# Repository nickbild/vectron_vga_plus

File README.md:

# Vectron VGA Plus

Vectron VGA Plus generates a 640x480@60Hz VGA signal and has an interface that works with retro computers or microcontrollers.

Screenshot of Vectron VGA Plus running a demo:

## How It Works

I previously built a massive 7400-logic based VGA generator called [Vectron VGA](https://github.com/nickbild/vectron_vga).  While it was a nice project to build, it is huge, and not very practical to keep around for use in lots of other projects.  I built Vectron VGA Plus as a much smaller, simpler alternative.

The key change that simplified the design was to use more RAM and less logic.  So, for example, instead of having counters and flip flops, etc. to time each horizontal sync, that logic is embedded in the data in memory.  This new design was also used to create a PCB, and the KiCad files are [here](https://github.com/nickbild/vectron_vga_plus/tree/main/vectron_vga_plus_design).

The general overview of the design goes like this: a 25.175 MHz pixel clock (divided in half by a flip flop) is used to trigger a chain of 4 bit counter chips.  These counters form an address in memory, and bits from the data stored at that memory location represent red, green, blue, horizontal sync, and vertical sync.  When the end of a frame is reached, magnitude comparators reset the counters, and it all starts over for the next frame.

Of course you also need to get data *in* to the RAM, so there are some buffer chips and mode selection signals to allow an external device (e.g. retro computer or microcontroller) to take over bus control and write RAM as needed.

As I mentioned, the 25.175 MHz clock has been divided by 2, which yields a viewable resolution of 320 horizontal pixels.  To keep logic simple, the vertical resolution is kept at 480 lines, technically giving an odd resolution of 320x480, but it is expected that in actual use, the external device is going to double up horizontal lines, giving a standard resolution of 320x240.  3-bit color was implemented, yielding a palette of 8 colors.

Since even non-visible screen regions need to be represented in the RAM (for blanking periods and V-sync/H-sync timings), RAM usage is higher -- 320x480 requires 210KB of video RAM (I used a 512KB chip that I had on hand, but a 256KB chip would be sufficient).  That's a bit extravagant for the 80s-esque 6502-based retro computers that I build, but it's also, I think, within bounds for a pure retro device (as opposed to using a microcontroller or FPGA).  In addition to the reduction in chip count, this design also pays off in flexibility; timings can be tweaked by adjusting the contents of memory, even after the PCB has been finalized.

## Media

An Arduino Mega 2560 sending images to Vectron VGA Plus:

Oops!  I picked the wrong footprint for my oscillator!  Fortunately, I could still solder the pins to the pads.

Schematic:

Breadboard prototype of circuit:

## Bill of Materials

- 1 x 25.175 MHz oscillator
- 1 x 74LS74AN
- 5 x 74LS161
- 2 x SN74LS682N
- 1 x SN74HC32N
- 1 x 74LS04N
- 2 x SN74LS245N
- 4 x SN74LS244N
- 1 x AS6C4008-55PCN
- 1 x 74LS273
- 3 x 200 ohm resistors
- 3 x 100 ohm resistors
- 2 x 200 uF electrolytic capacitors
- 1 x VGA connector
- 36 x female header pins

## About the Author

[Nick A. Bild, MS](https://nickbild79.firebaseapp.com/#!/)

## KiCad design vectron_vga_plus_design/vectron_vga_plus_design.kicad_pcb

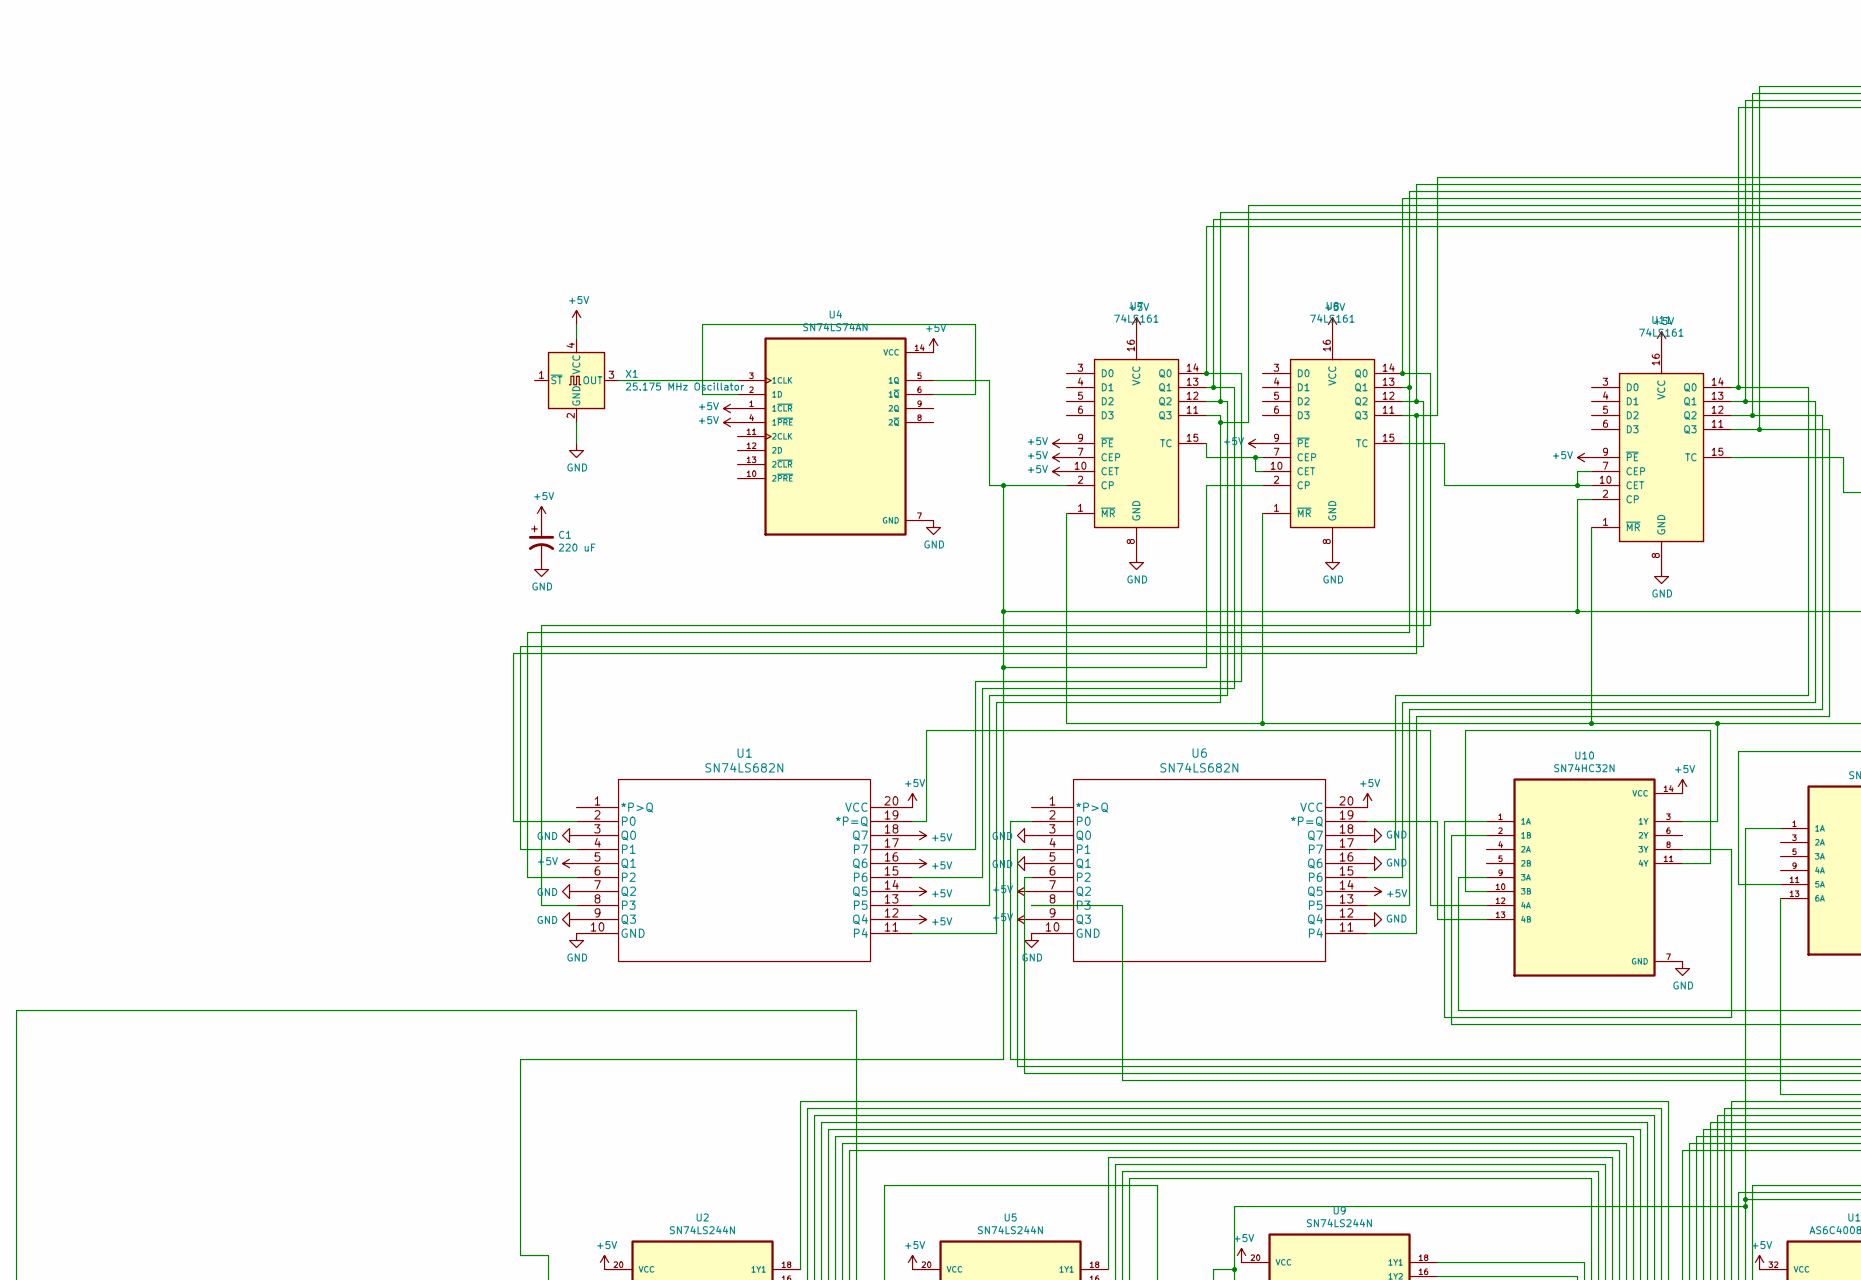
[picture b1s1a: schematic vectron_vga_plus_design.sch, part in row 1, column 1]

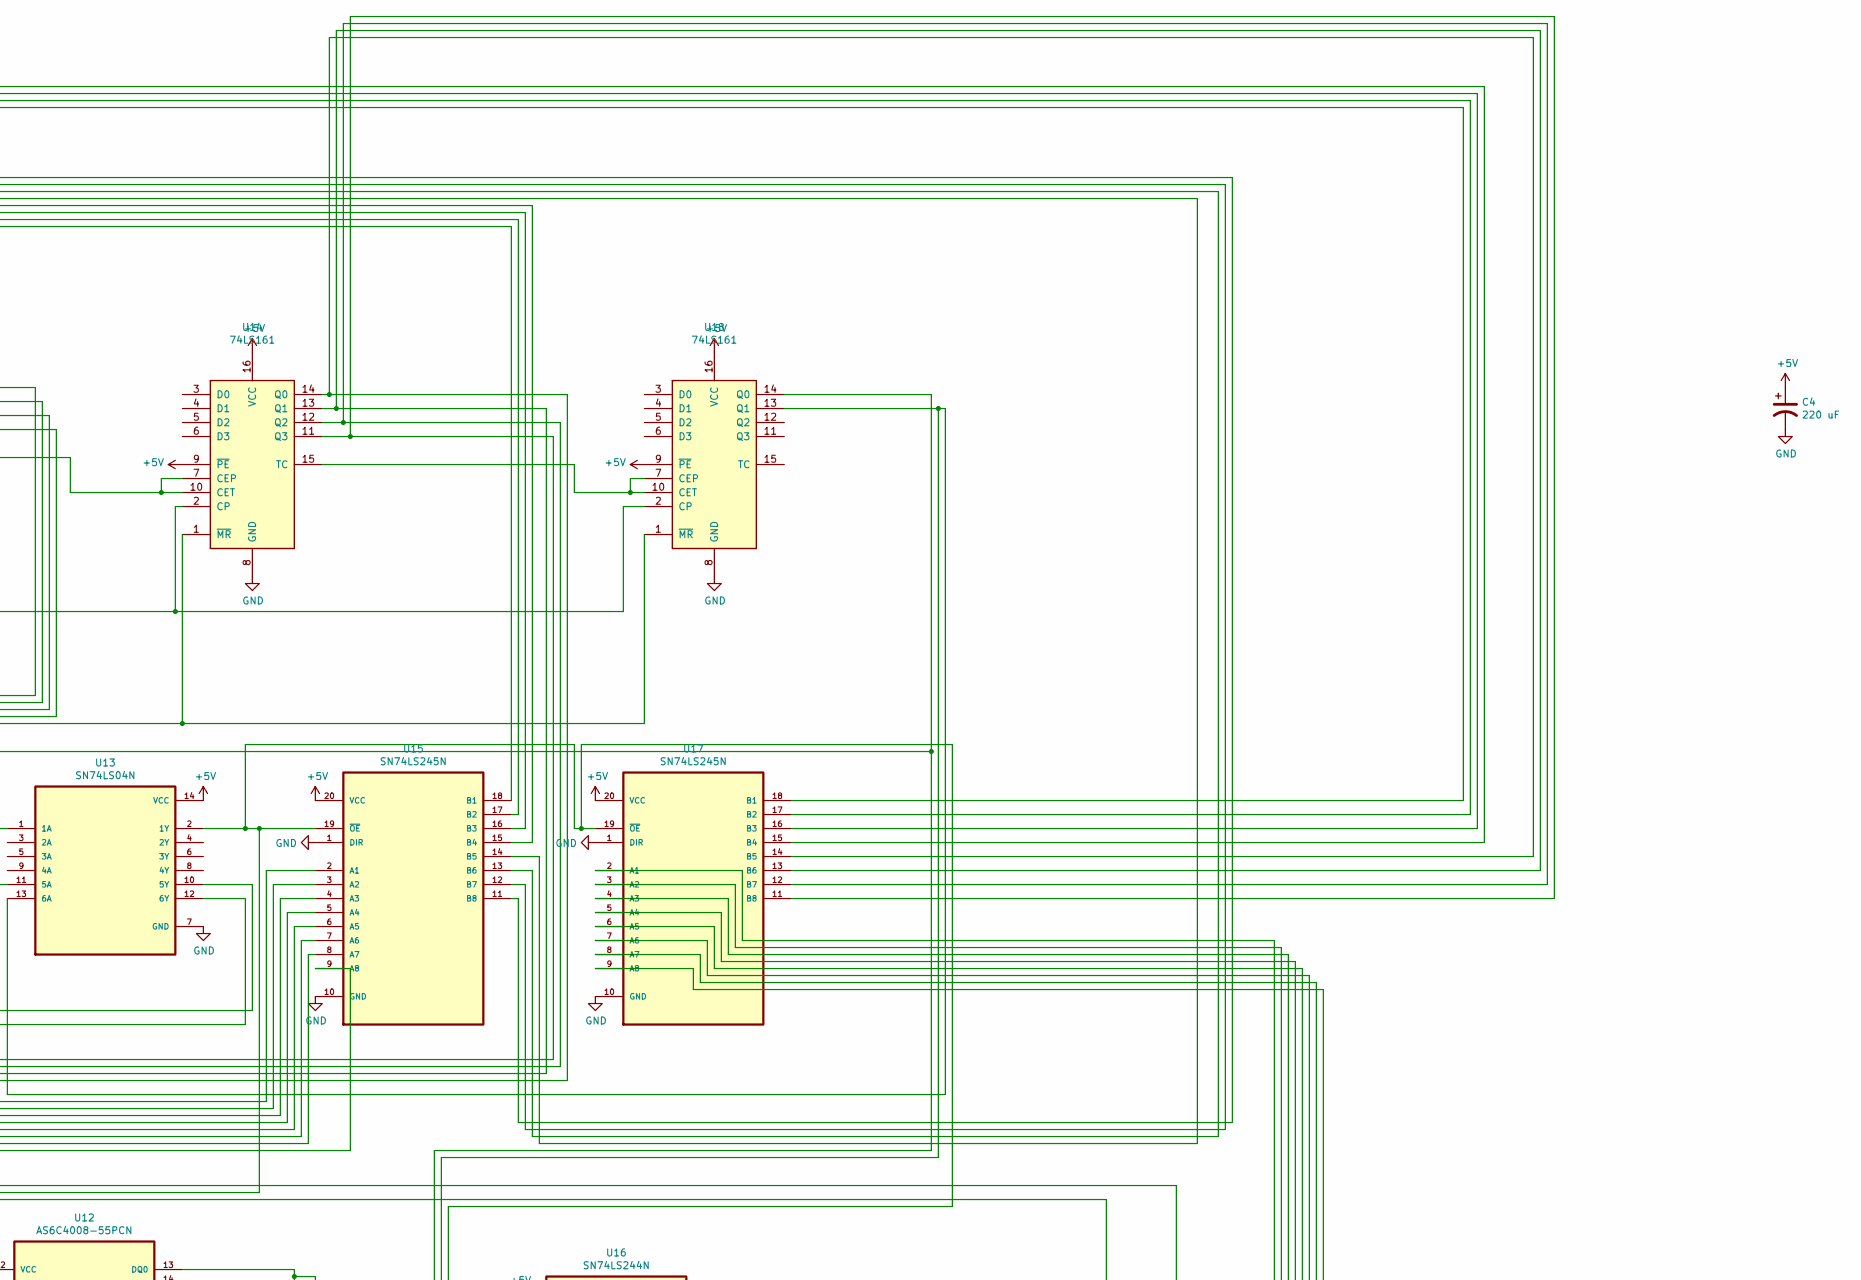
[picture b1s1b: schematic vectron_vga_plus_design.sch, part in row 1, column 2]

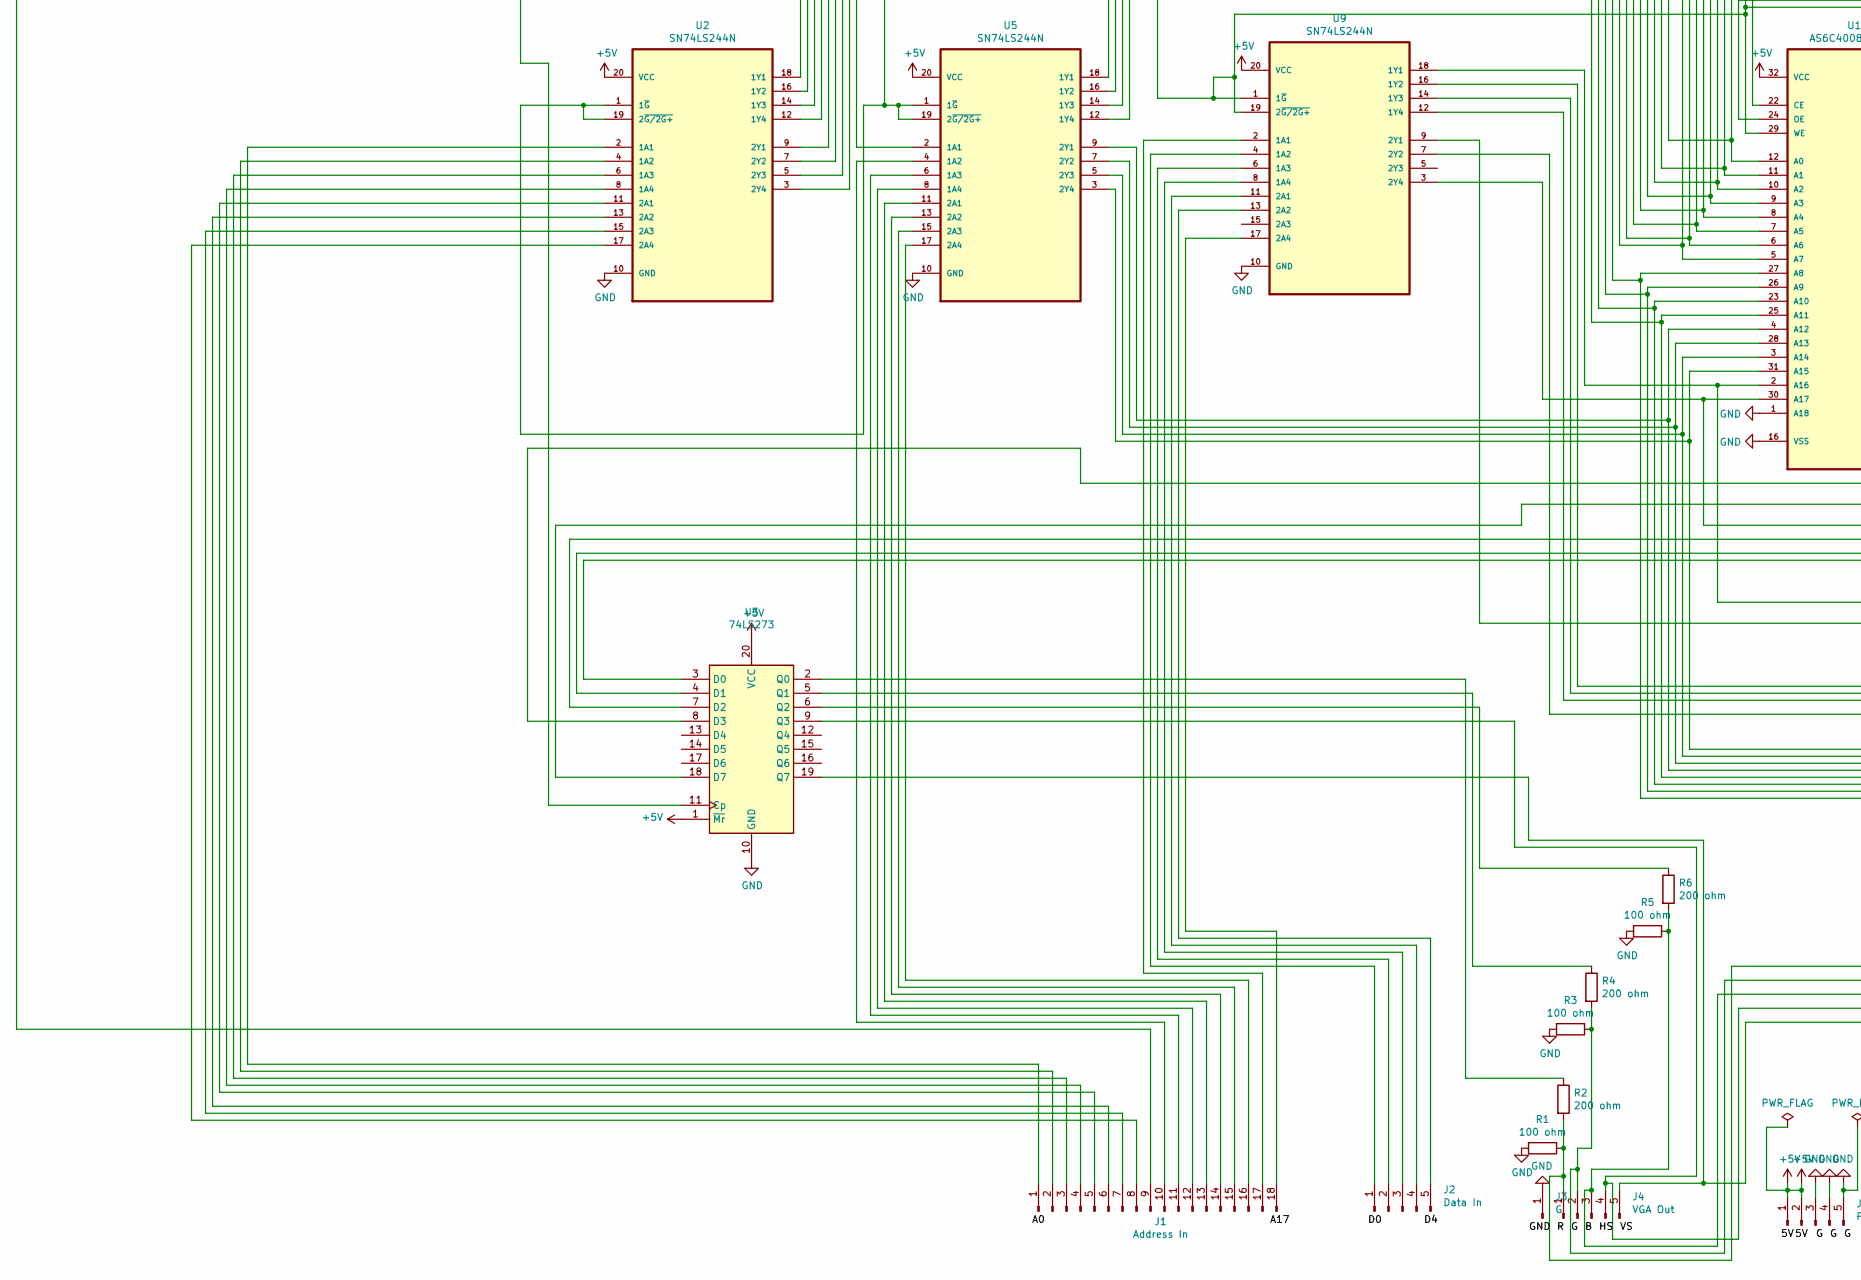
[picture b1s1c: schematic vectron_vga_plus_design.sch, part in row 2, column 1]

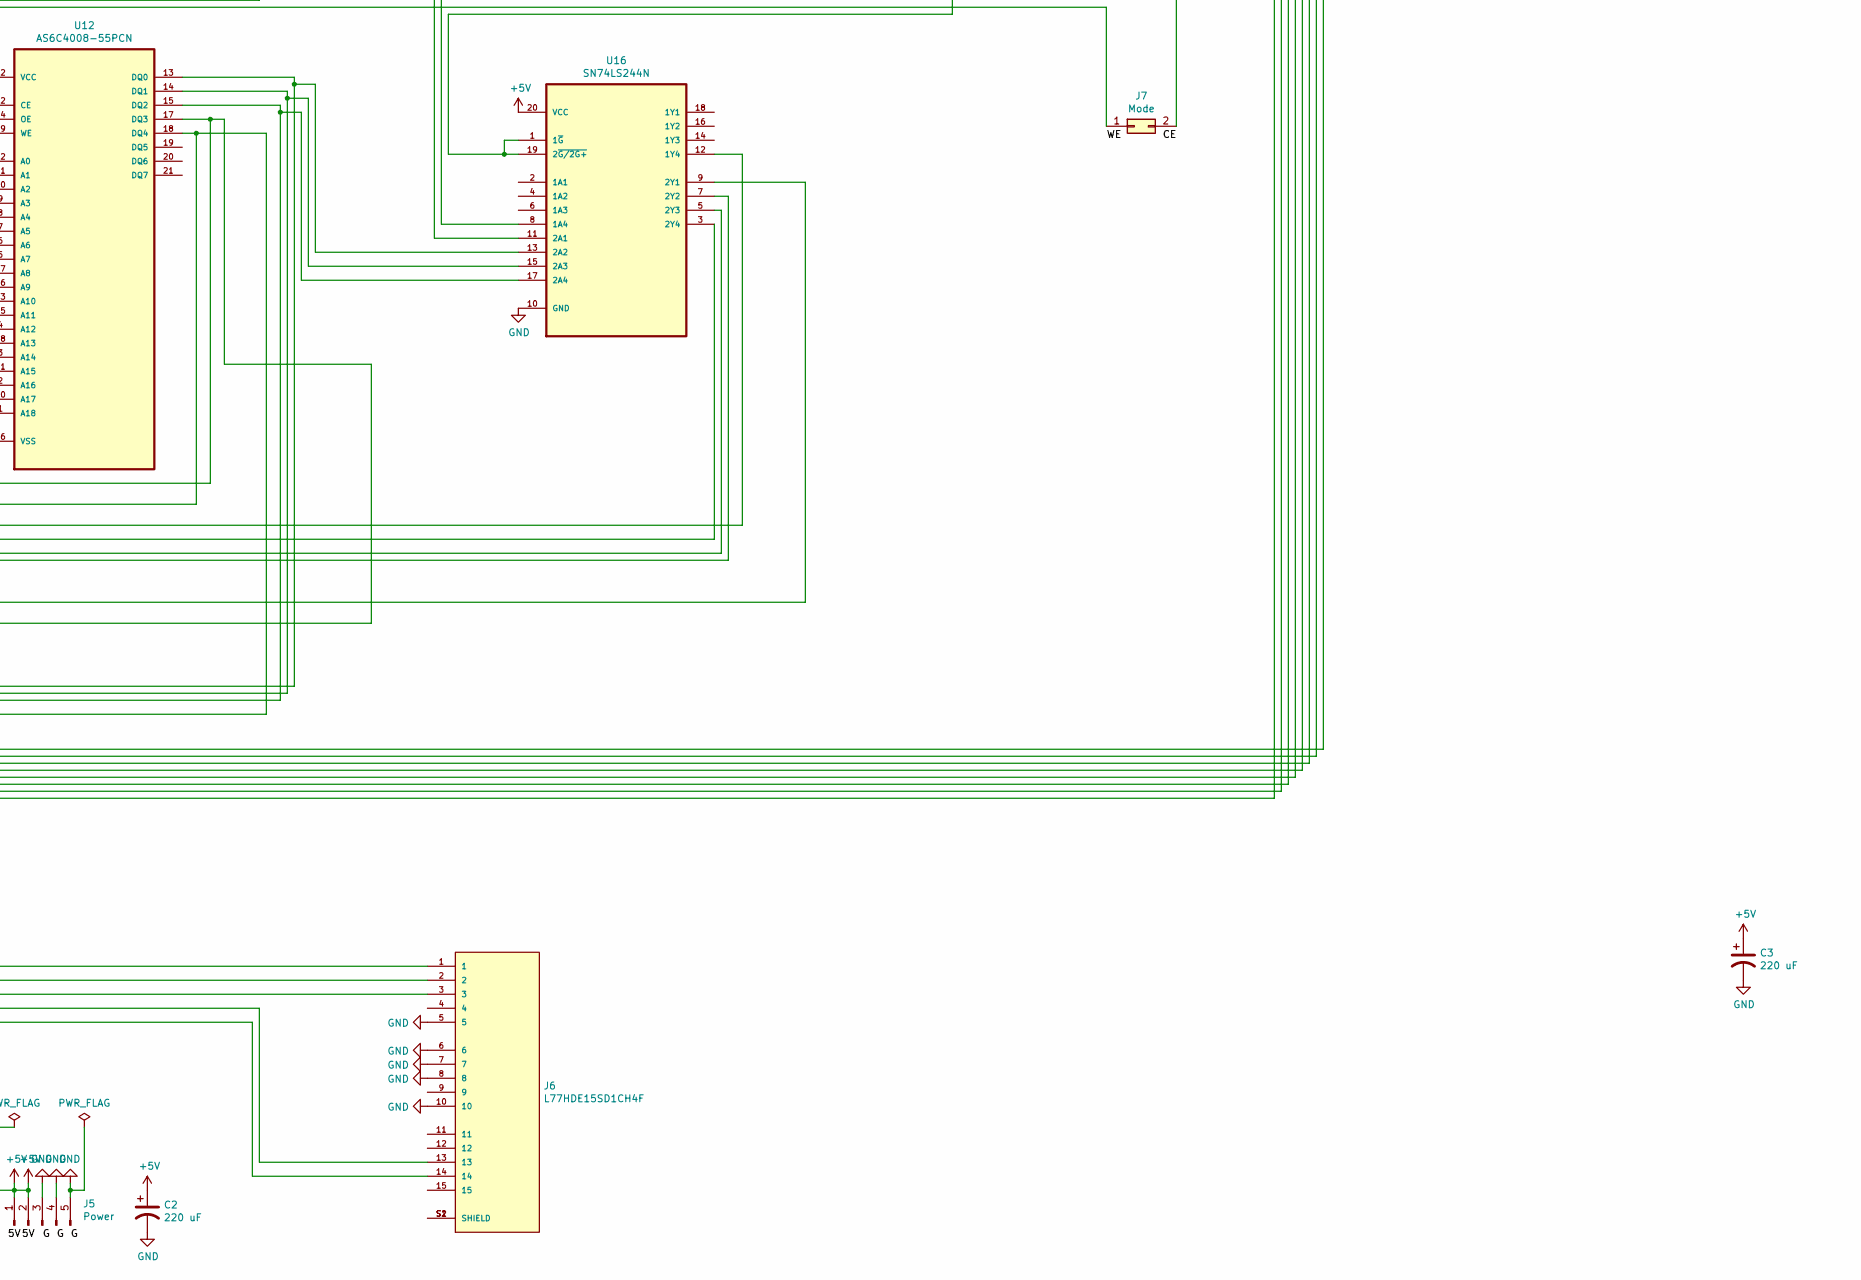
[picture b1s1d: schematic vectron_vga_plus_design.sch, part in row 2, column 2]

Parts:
C1, C2, C3, C4: 220 uF; CP_Radial_D10.0mm_P7.50mm
J1: Address In; PinHeader_1x18_P2.54mm_Horizontal
J2: Data In; PinHeader_1x05_P2.54mm_Horizontal
J3: G; PinHeader_1x01_P2.54mm_Horizontal
J4: VGA Out; PinHeader_1x05_P2.54mm_Horizontal
J5: Power; PinHeader_1x05_P2.54mm_Horizontal
J6: L77HDE15SD1CH4F; AMPHENOL_L77HDE15SD1CH4F; PARTREV N/A
J7: Mode; PinHeader_1x02_P2.54mm_Horizontal
R1, R3, R5: 100 ohm; R_Axial_DIN0207_L6.3mm_D2.5mm_P7.62mm_Horizontal
R2, R4, R6: 200 ohm; R_Axial_DIN0207_L6.3mm_D2.5mm_P7.62mm_Horizontal
U1, U6: SN74LS682N
U2, U5, U9, U16: SN74LS244N; DIP254P762X508-20; MPN SN74LS244N
U3: 74LS273; DIP254P762X508-20
U4: SN74LS74AN; DIP794W45P254L1969H508Q14
U7, U8, U11, U14, U18: 74LS161; SN74LS161AN
U10: SN74HC32N; DIP794W45P254L1969H508Q14
U12: AS6C4008-55PCN; DIP254P1524X393-32; MPN AS6C4008-55PCN
U13: SN74LS04N; DIP794W45P254L1969H508Q14
U15, U17: SN74LS245N; DIP254P762X508-20; MPN SN74LS245N
X1: 25.175 MHz Oscillator; Oscillator_SMD_SeikoEpson_SG8002CA-4Pin_7.0x5.0mm

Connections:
+5V: C1.1, C2.1, C3.1, C4.1, J5.1, J5.2, U1.5 (Q1), U1.12 (Q4), U1.14 (Q5), U1.16 (Q6), U1.18 (Q7), U1.20 (VCC), U2.20 (VCC), U3.1 (~Mr), U3.20 (VCC), U4.1 (1~CLR), U4.4 (1~PRE), U4.14 (VCC), U5.20 (VCC), U6.7 (Q2), U6.9 (Q3), U6.14 (Q5), U6.20 (VCC), U7.7 (CEP), U7.9 (~PE), U7.10 (CET), U7.16 (VCC), U8.9 (~PE), U8.16 (VCC), U9.20 (VCC), U10.14 (VCC), U11.9 (~PE), U11.16 (VCC), U12.32 (VCC), U13.14 (VCC), U14.9 (~PE), U14.16 (VCC), U15.20 (VCC), U16.20 (VCC), U17.20 (VCC), U18.9 (~PE), U18.16 (VCC), X1.4 (VCC)
/B: J4.3, J6.3, R5.1, R6.2
/G: J4.2, J6.2, R3.1, R4.2
GND: C1.2, C2.2, C3.2, C4.2, J3.1, J5.3, J5.4, J5.5, J6.5, J6.6, J6.7, J6.8, J6.10, R1.2, R3.2, R5.2, U1.3 (Q0), U1.7 (Q2), U1.9 (Q3), U1.10 (GND), U2.10 (GND), U3.10 (GND), U4.7 (GND), U5.10 (GND), U6.3 (Q0), U6.5 (Q1), U6.10 (GND), U6.12 (Q4), U6.16 (Q6), U6.18 (Q7), U7.8 (GND), U8.8 (GND), U9.10 (GND), U10.7 (GND), U11.8 (GND), U12.1 (A18), U12.16 (VSS), U13.7 (GND), U14.8 (GND), U15.1 (DIR), U15.10 (GND), U16.10 (GND), U17.1 (DIR), U17.10 (GND), U18.8 (GND), X1.2 (GND)
unnamed: J1.1, U2.2 (1A1)
unnamed: J1.2, U2.4 (1A2)
unnamed: J1.3, U2.6 (1A3)
unnamed: J1.4, U2.8 (1A4)
unnamed: J1.5, U2.11 (2A1)
unnamed: J1.6, U2.13 (2A2)
unnamed: J1.7, U2.15 (2A3)
unnamed: J1.8, U2.17 (2A4)
unnamed: J1.9, U5.2 (1A1)
unnamed: J1.10, U5.4 (1A2)
unnamed: J1.11, U5.6 (1A3)
unnamed: J1.12, U5.8 (1A4)
unnamed: J1.13, U5.11 (2A1)
unnamed: J1.14, U5.13 (2A2)
unnamed: J1.15, U5.15 (2A3)
unnamed: J1.16, U5.17 (2A4)
unnamed: J1.17, U9.2 (1A1)
unnamed: J1.18, U9.17 (2A4)
unnamed: J2.1, U9.4 (1A2)
unnamed: J2.2, U9.6 (1A3)
unnamed: J2.3, U9.8 (1A4)
unnamed: J2.4, U9.11 (2A1)
unnamed: J2.5, U9.13 (2A2)
unnamed: J4.1, J6.1, R1.1, R2.2
unnamed: J4.4, J6.13, U3.9 (Q3)
unnamed: J4.5, J6.14, U3.19 (Q7)
unnamed: J6.S1 (SHIELD), J6.S2 (SHIELD)
unnamed: J7.1, U2.1 (1~G), U2.19 (2~G/2G+), U5.1 (1~G), U5.19 (2~G/2G+), U9.1 (1~G), U9.19 (2~G/2G+), U12.29 (WE), U13.1 (1A)
unnamed: J7.2, U12.22 (CE)
unnamed: R2.1, U3.2 (Q0)
unnamed: R4.1, U3.5 (Q1)
unnamed: R6.1, U3.6 (Q2)
unnamed: U1.2 (P0), U8.11 (Q3), U15.11 (B8)
unnamed: U1.4 (P1), U8.12 (Q2), U15.12 (B7)
unnamed: U1.6 (P2), U8.13 (Q1), U15.13 (B6)
unnamed: U1.8 (P3), U8.14 (Q0), U15.14 (B5)
unnamed: U1.11 (P4), U7.11 (Q3), U15.15 (B4)
unnamed: U1.13 (P5), U7.12 (Q2), U15.16 (B3)
unnamed: U1.15 (P6), U7.13 (Q1), U15.17 (B2)
unnamed: U1.17 (P7), U7.14 (Q0), U15.18 (B1)
unnamed: U1.19 (*P=Q), U10.12 (4A)
unnamed: U4.2 (1D), U4.6 (1~Q)
unnamed: U4.3 (1CLK), X1.3 (OUT)
unnamed: U7.15 (TC), U8.7 (CEP), U8.10 (CET)
unnamed: U10.1 (1A), U10.8 (3Y)
unnamed: U10.2 (1B), U13.12 (6Y)
unnamed: U7.1 (~MR), U8.1 (~MR), U10.3 (1Y), U11.1 (~MR), U14.1 (~MR), U18.1 (~MR)
unnamed: U10.9 (3A), U13.10 (5Y)
unnamed: U10.10 (3B), U10.11 (4Y)
unnamed: U6.19 (*P=Q), U10.13 (4B)
unnamed: U3.11 (Cp), U4.5 (1Q), U7.2 (CP), U8.2 (CP), U11.2 (CP), U14.2 (CP), U18.2 (CP)
unnamed: U8.15 (TC), U11.7 (CEP), U11.10 (CET)
unnamed: U6.11 (P4), U11.11 (Q3), U17.15 (B4)
unnamed: U6.13 (P5), U11.12 (Q2), U17.16 (B3)
unnamed: U6.15 (P6), U11.13 (Q1), U17.17 (B2)
unnamed: U6.17 (P7), U11.14 (Q0), U17.18 (B1)
unnamed: U11.15 (TC), U14.7 (CEP), U14.10 (CET)
unnamed: U9.18 (1Y1), U12.2 (A16), U16.9 (2Y1)
unnamed: U5.5 (2Y3), U12.3 (A14), U17.8 (A7)
unnamed: U5.9 (2Y1), U12.4 (A12), U17.6 (A5)
unnamed: U2.3 (2Y4), U12.5 (A7), U15.9 (A8)
unnamed: U2.5 (2Y3), U12.6 (A6), U15.8 (A7)
unnamed: U2.7 (2Y2), U12.7 (A5), U15.7 (A6)
unnamed: U2.9 (2Y1), U12.8 (A4), U15.6 (A5)
unnamed: U2.12 (1Y4), U12.9 (A3), U15.5 (A4)
unnamed: U2.14 (1Y3), U12.10 (A2), U15.4 (A3)
unnamed: U2.16 (1Y2), U12.11 (A1), U15.3 (A2)
unnamed: U2.18 (1Y1), U12.12 (A0), U15.2 (A1)
unnamed: U9.16 (1Y2), U12.13 (DQ0), U16.13 (2A2)
unnamed: U9.14 (1Y3), U12.14 (DQ1), U16.15 (2A3)
unnamed: U9.12 (1Y4), U12.15 (DQ2), U16.17 (2A4)
unnamed: U3.8 (D3), U9.9 (2Y1), U12.17 (DQ3)
unnamed: U3.18 (D7), U9.7 (2Y2), U12.18 (DQ4)
unnamed: U5.14 (1Y3), U12.23 (A10), U17.4 (A3)
unnamed: U12.24 (OE), U13.2 (1Y), U15.19 (~OE), U16.1 (1~G), U16.19 (2~G/2G+), U17.19 (~OE)
unnamed: U5.12 (1Y4), U12.25 (A11), U17.5 (A4)
unnamed: U5.16 (1Y2), U12.26 (A9), U17.3 (A2)
unnamed: U5.18 (1Y1), U12.27 (A8), U17.2 (A1)
unnamed: U5.7 (2Y2), U12.28 (A13), U17.7 (A6)
unnamed: U9.3 (2Y4), U12.30 (A17), U16.12 (1Y4)
unnamed: U5.3 (2Y4), U12.31 (A15), U17.9 (A8)
unnamed: U13.11 (5A), U16.11 (2A1), U18.14 (Q0)
unnamed: U13.13 (6A), U16.8 (1A4), U18.13 (Q1)
unnamed: U6.2 (P0), U14.11 (Q3), U17.11 (B8)
unnamed: U6.4 (P1), U14.12 (Q2), U17.12 (B7)
unnamed: U6.6 (P2), U14.13 (Q1), U17.13 (B6)
unnamed: U6.8 (P3), U14.14 (Q0), U17.14 (B5)
unnamed: U14.15 (TC), U18.7 (CEP), U18.10 (CET)
unnamed: U3.7 (D2), U16.3 (2Y4)
unnamed: U3.4 (D1), U16.5 (2Y3)
unnamed: U3.3 (D0), U16.7 (2Y2)

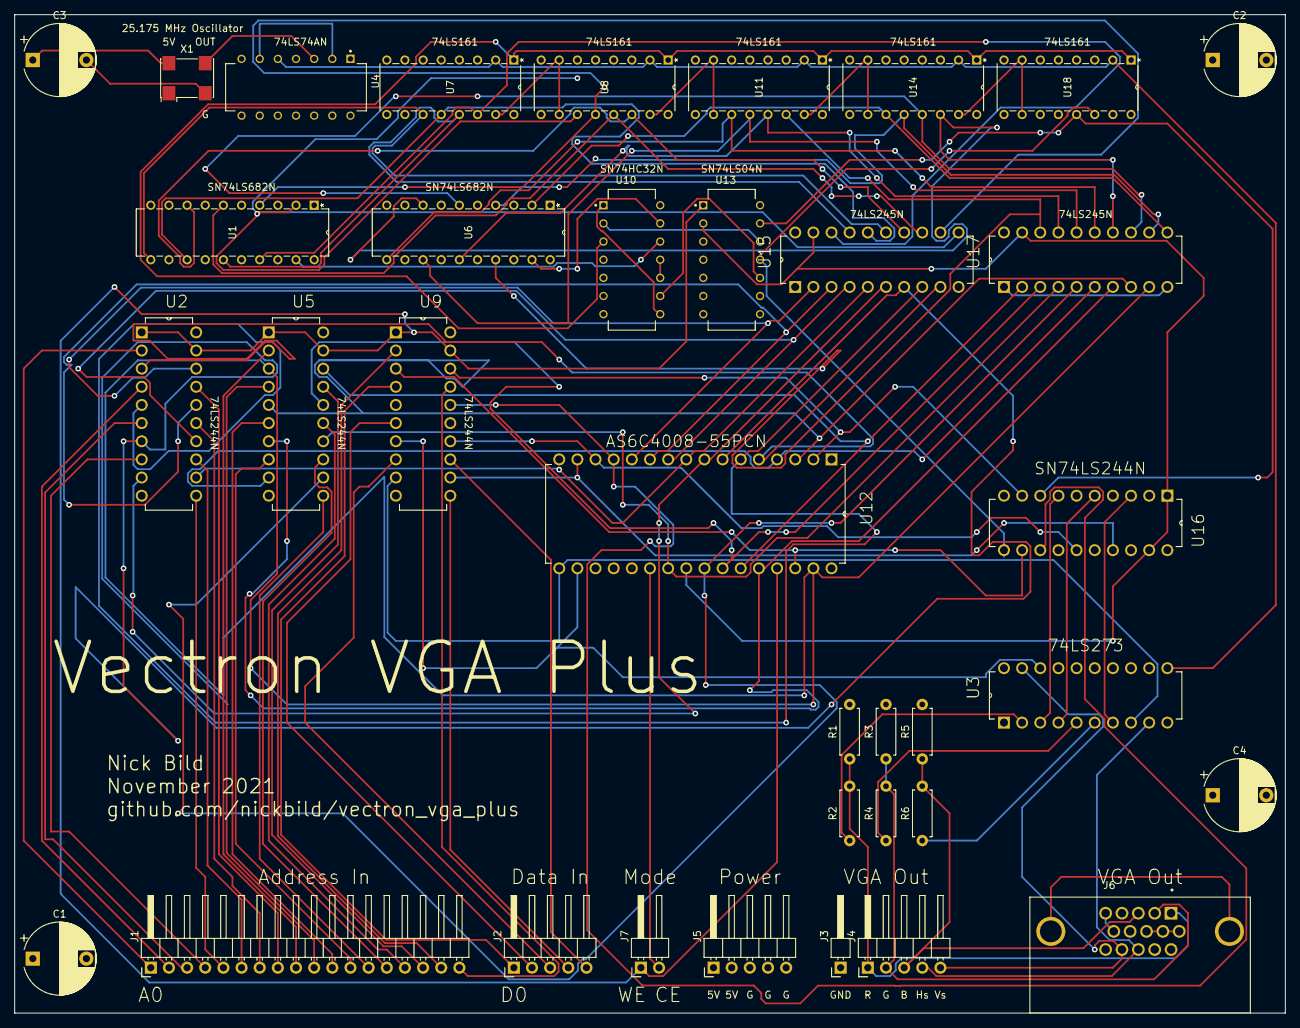
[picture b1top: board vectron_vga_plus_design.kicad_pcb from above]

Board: 4 copper layers, 177.8 x 139.7 mm, 36 parts (0 on the bottom side), 95 nets.

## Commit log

2021-11-19 Initial commit.
2021-11-19 Add Arduino Mega code for testing.
2021-11-21 Save progress on design files.
2021-12-05 Fix Arduino tester and add gerber files.
2021-12-05 Update test pattern.
2021-12-05 Add images.
2021-12-05 Update documentation.
2021-12-05 Add demo graphics.
2021-12-16 Create LICENSE

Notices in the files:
parts and their libraries:
Copyright 2021 Accelerated Designs. All rights reserved.
